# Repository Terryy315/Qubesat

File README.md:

NOTE: MOST PROJECTS ARE IN ACTIVE DEVELOPMENT

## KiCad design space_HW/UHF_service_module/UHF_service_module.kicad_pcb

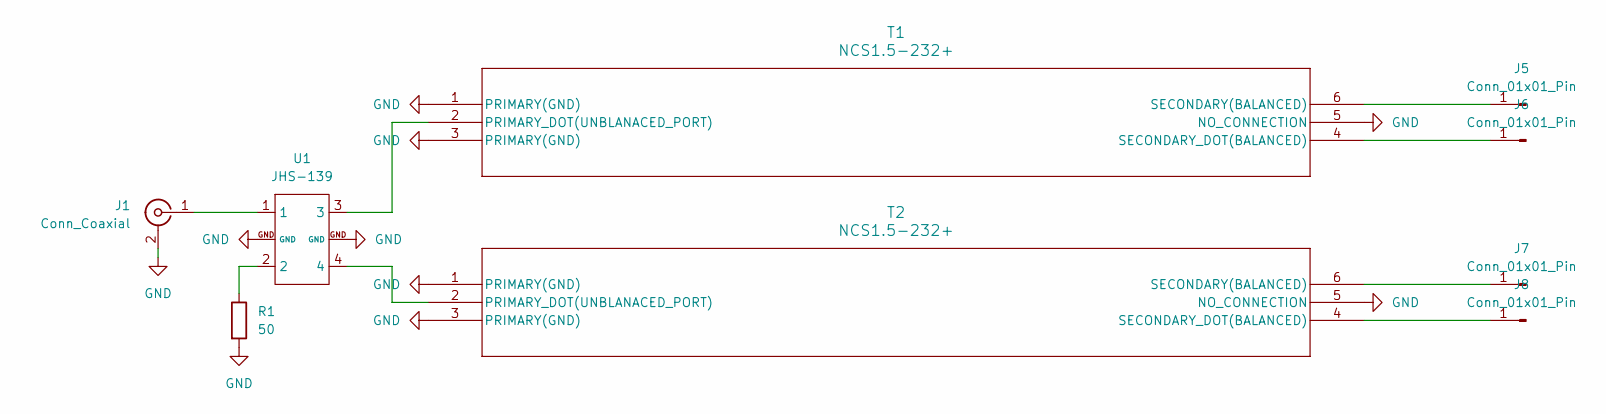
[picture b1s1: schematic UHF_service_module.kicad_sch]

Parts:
J1: Conn_Coaxial; MMCX_Molex_73415-0961_Horizontal_1.6mm-PCB
J5, J6, J7, J8: Conn_01x01_Pin; SolderWirePad_1x01_SMD_1.5x3mm
R1: 50; R_0402_1005Metric
T1, T2: NCS1.5-232+; GE0805C-9_MNC
U1: JHS-139

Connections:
GND: J1.2 (Ext), R1.2, T1.1 (PRIMARY(GND)), T1.3 (PRIMARY(GND)), T1.5 (NO_CONNECTION), T2.1 (PRIMARY(GND)), T2.3 (PRIMARY(GND)), T2.5 (NO_CONNECTION), U1.GND
unnamed: J1.1 (In), U1.1
unnamed: J5.1, T1.6 (SECONDARY(BALANCED))
unnamed: J6.1, T1.4 (SECONDARY_DOT(BALANCED))
unnamed: J7.1, T2.6 (SECONDARY(BALANCED))
unnamed: J8.1, T2.4 (SECONDARY_DOT(BALANCED))
unnamed: R1.1, U1.2
unnamed: T1.2 (PRIMARY_DOT(UNBLANACED_PORT)), U1.3
unnamed: T2.2 (PRIMARY_DOT(UNBLANACED_PORT)), U1.4

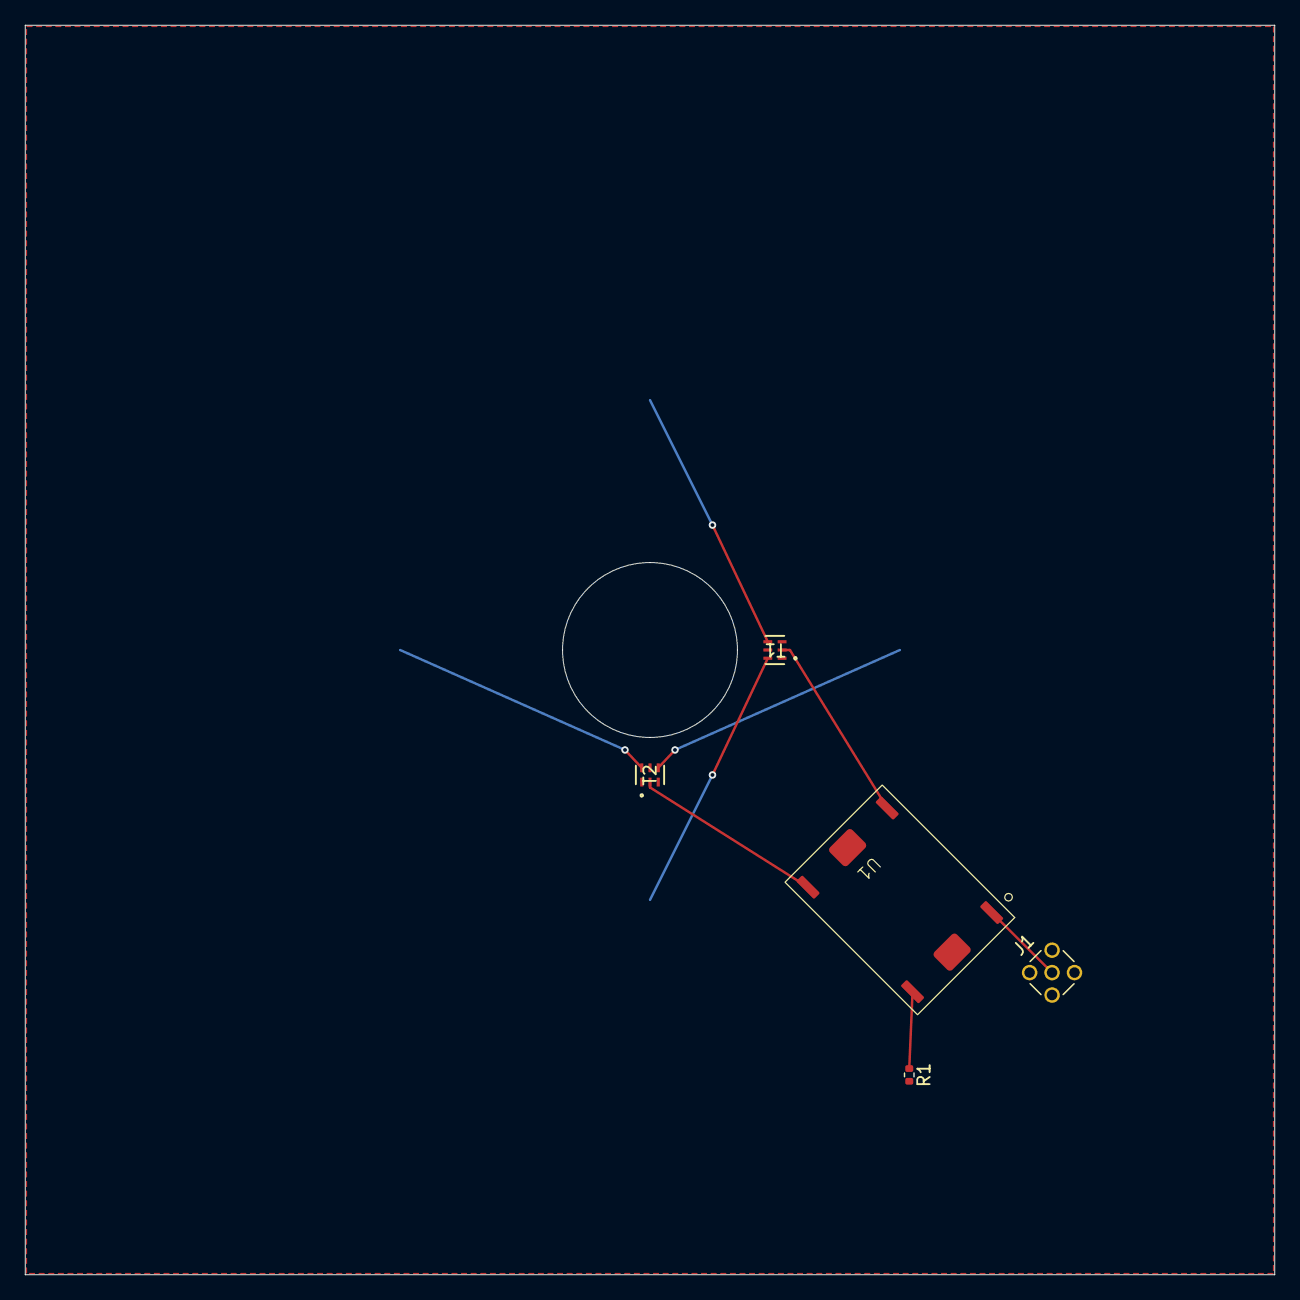
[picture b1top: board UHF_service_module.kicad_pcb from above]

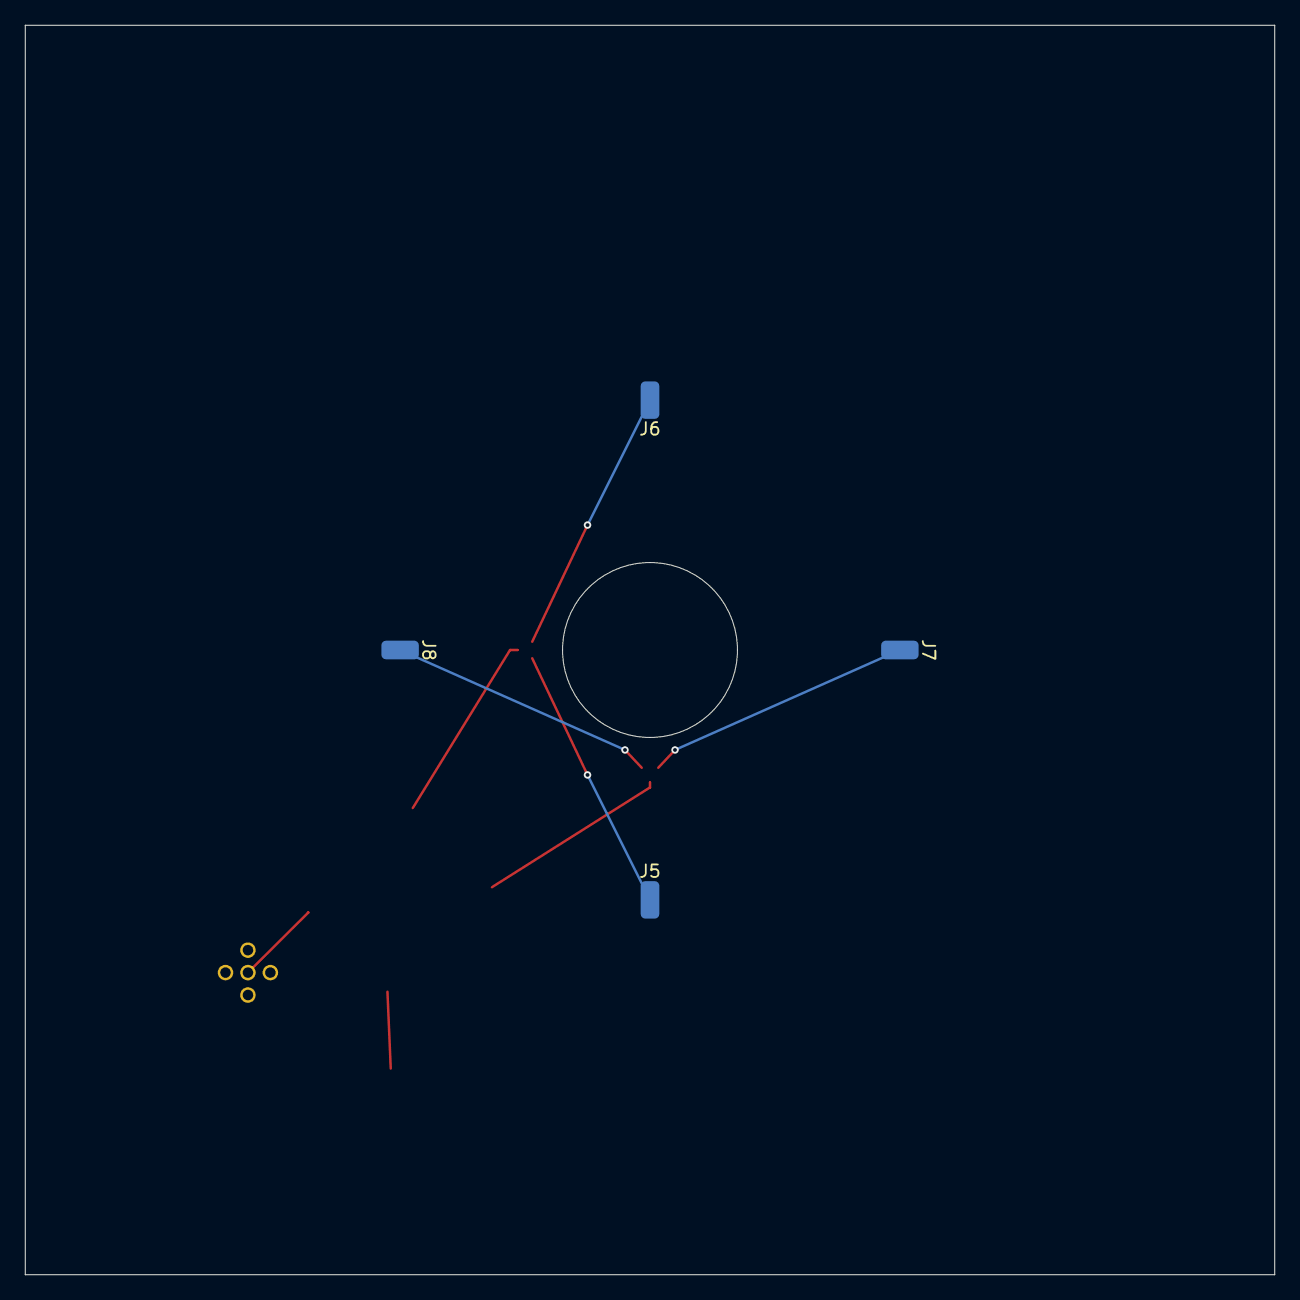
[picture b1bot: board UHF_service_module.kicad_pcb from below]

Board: 2 copper layers, 100.0 x 100.0 mm, 9 parts (4 on the bottom side), 9 nets.

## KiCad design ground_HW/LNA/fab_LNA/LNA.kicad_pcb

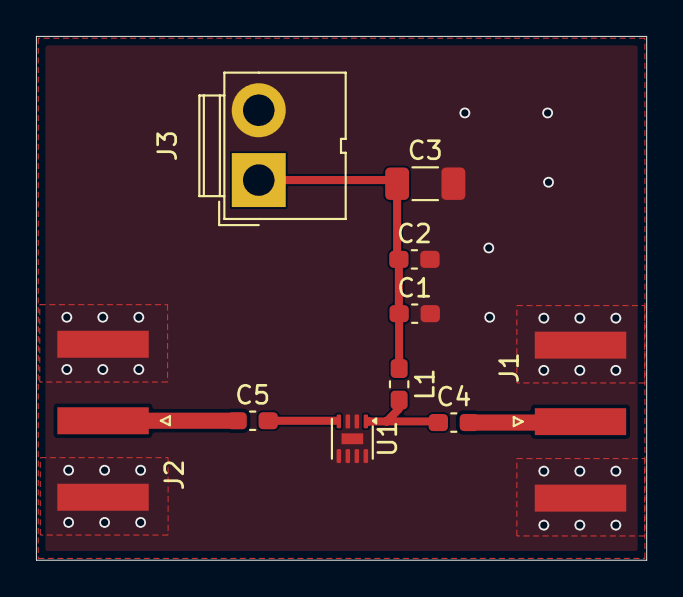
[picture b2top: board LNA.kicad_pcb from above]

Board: 2 copper layers, 33.9 x 29.1 mm, 10 parts (0 on the bottom side), 6 nets.

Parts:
C1, C2, C4, C5: C; C_0603_1608Metric_Pad1.08x0.95mm_HandSolder
C3: C; C_1206_3216Metric_Pad1.33x1.80mm_HandSolder
J1, J2: Conn_Coaxial; SMA_Amphenol_132289_EdgeMount
J3: Conn_01x02_Pin; JWT_A3963_1x02_P3.96mm_Vertical
L1: L; L_0603_1608Metric_Pad1.05x0.95mm_HandSolder
U1: SGL0622Z; DFN-8-1EP_2x2mm_P0.5mm_EP0.6x1.2mm

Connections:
/RF_filter_0.45mm: C1.1, C2.1, C3.1, J3.1, L1.1
/RF_in_0.45mm: C5.2, U1.4
/RF_in_1.1mm: C5.1, J2.1 (In)
/RF_out_0.45mm: C4.1, L1.2, U1.1
/RF_out_1.1mm: C4.2, J1.1 (In)
GND: C1.2, C2.2, C3.2, J1.2 (Ext), J2.2 (Ext), J3.2, U1.2 (GND), U1.3 (GND), U1.5 (GND), U1.6 (GND), U1.7 (GND), U1.8 (GND), U1.9 (GND)

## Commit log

2026-05-26 QUBESAT
2026-06-07 added space segment
2026-06-07 Added antennas
